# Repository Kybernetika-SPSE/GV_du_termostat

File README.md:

# GV_du_termostat
práce z hodiny 19.1.2026

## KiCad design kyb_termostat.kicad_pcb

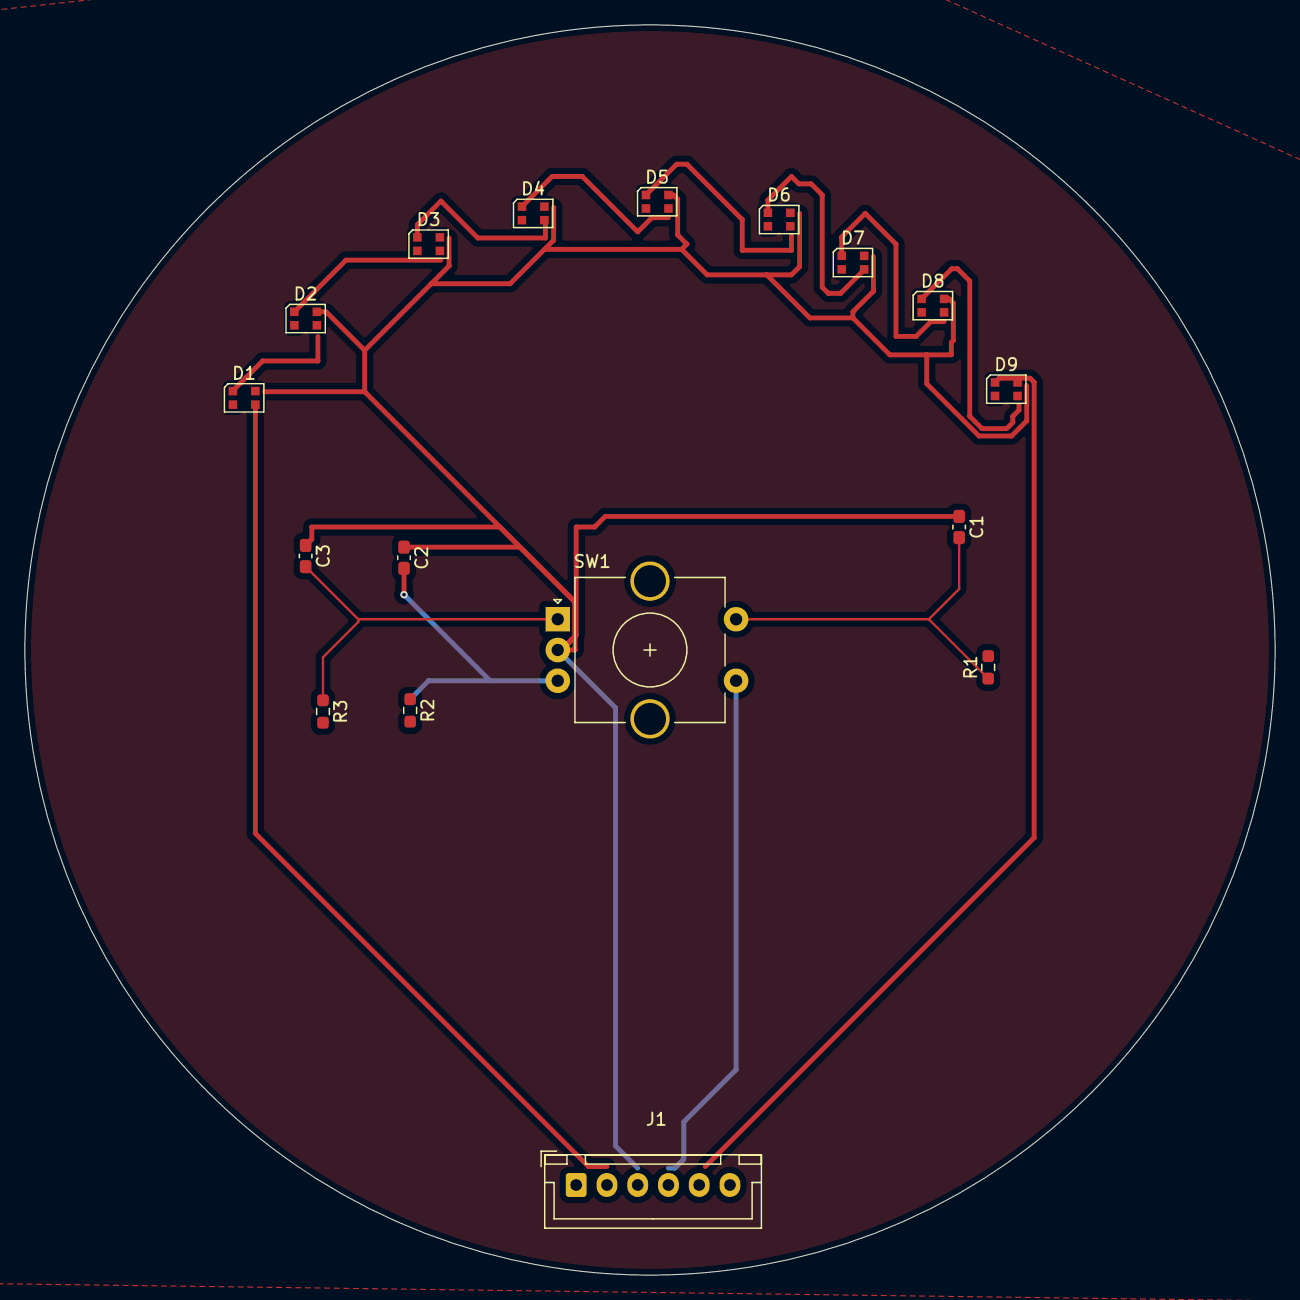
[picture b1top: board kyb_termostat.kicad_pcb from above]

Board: 2 copper layers, 101.7 x 101.7 mm, 17 parts (0 on the bottom side), 7 nets.

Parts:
C1, C2, C3: 47nF; C_0603_1608Metric_Pad1.08x0.95mm_HandSolder
D1, D2, D3, D4, D5, D6, D7, D8, D9: WS2812B-2020; LED_WS2812B-2020_PLCC4_2.0x2.0mm
J1: Conn_01x06; JST_XH_B6B-XH-A_1x06_P2.50mm_Vertical
R1, R2, R3: 10k; R_0603_1608Metric_Pad0.98x0.95mm_HandSolder
SW1: RotaryEncoder_Switch_MP; RotaryEncoder_Alps_EC11E-Switch_Vertical_H20mm_CircularMoun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

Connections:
+3V3: C1.1, C2.1, C3.1, D2.4 (VDD), D5.4 (VDD), D8.4 (VDD), SW1.C, SW1.S1
/DC: C3.2, R3.1, SW1.A
/SW: C1.2, R1.1, SW1.S2
GND: D2.2 (VSS), D5.2 (VSS), D8.2 (VSS), R1.2, R2.2, R3.2, SW1.MP
unnamed: C2.2, R2.1, SW1.B
unnamed: D2.1 (DOUT), D5.3 (DIN)
unnamed: D5.1 (DOUT), D8.3 (DIN)
